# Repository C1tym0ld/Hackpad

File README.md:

# Hackpad

## Pictures

# BOM
- 3d printed Case
- XIAO rp2040
- 10 SK6812 MINI-E LEDs
- 8 Switches
- 8 Key Caps
- 8x Through-hole 1N4148 Diodes 
- M3x16mm screws x4
- M3x5mx4mm heatset inserts x4
- VIA support!

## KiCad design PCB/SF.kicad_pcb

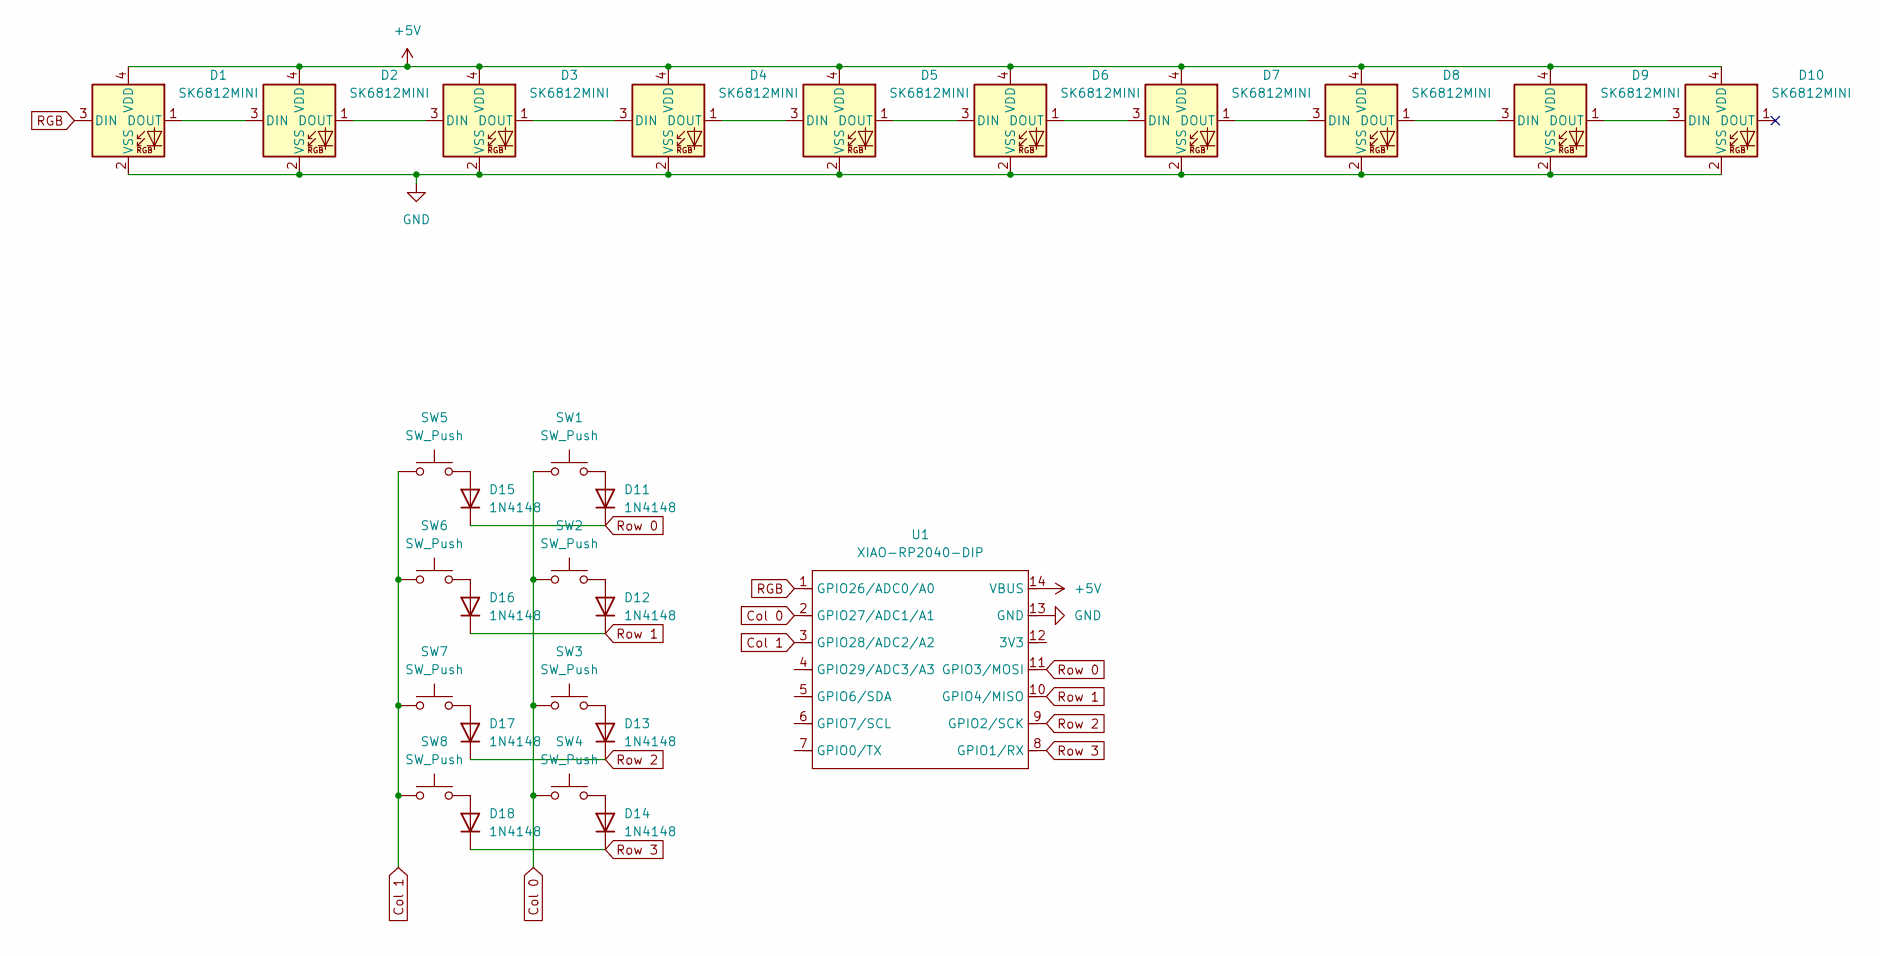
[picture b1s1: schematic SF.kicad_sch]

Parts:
D1, D2, D3, D4, D5, D6, D7, D8, D9, D10: SK6812MINI; LED_SK6812MINI_PLCC4_3.5x3.5mm_P1.75mm
D11, D12, D13, D14, D15, D16, D17, D18: 1N4148; D_DO-35_SOD27_P7.62mm_Horizontal
SW1, SW2, SW3, SW4, SW5, SW6, SW7, SW8: SW_Push; SW_Cherry_MX_1.00u_PCB
U1: XIAO-RP2040-DIP

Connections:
+5V: D1.4 (VDD), D2.4 (VDD), D3.4 (VDD), D4.4 (VDD), D5.4 (VDD), D6.4 (VDD), D7.4 (VDD), D8.4 (VDD), D9.4 (VDD), D10.4 (VDD), U1.14 (VBUS)
Col 0: SW1.1, SW2.1, SW3.1, SW4.1, U1.2 (GPIO27/ADC1/A1)
Col 1: SW5.1, SW6.1, SW7.1, SW8.1, U1.3 (GPIO28/ADC2/A2)
GND: D1.2 (VSS), D2.2 (VSS), D3.2 (VSS), D4.2 (VSS), D5.2 (VSS), D6.2 (VSS), D7.2 (VSS), D8.2 (VSS), D9.2 (VSS), D10.2 (VSS), U1.13 (GND)
unnamed: D1.1 (DOUT), D2.3 (DIN)
unnamed: D2.1 (DOUT), D3.3 (DIN)
unnamed: D3.1 (DOUT), D4.3 (DIN)
unnamed: D4.1 (DOUT), D5.3 (DIN)
unnamed: D5.1 (DOUT), D6.3 (DIN)
unnamed: D6.1 (DOUT), D7.3 (DIN)
unnamed: D7.1 (DOUT), D8.3 (DIN)
unnamed: D8.1 (DOUT), D9.3 (DIN)
unnamed: D9.1 (DOUT), D10.3 (DIN)
unnamed: D11.2 (A), SW1.2
unnamed: D12.2 (A), SW2.2
unnamed: D13.2 (A), SW3.2
unnamed: D14.2 (A), SW4.2
unnamed: D15.2 (A), SW5.2
unnamed: D16.2 (A), SW6.2
unnamed: D17.2 (A), SW7.2
unnamed: D18.2 (A), SW8.2
RGB: D1.3 (DIN), U1.1 (GPIO26/ADC0/A0)
Row 0: D11.1 (K), D15.1 (K), U1.11 (GPIO3/MOSI)
Row 1: D12.1 (K), D16.1 (K), U1.10 (GPIO4/MISO)
Row 2: D13.1 (K), D17.1 (K), U1.9 (GPIO2/SCK)
Row 3: D14.1 (K), D18.1 (K), U1.8 (GPIO1/RX)

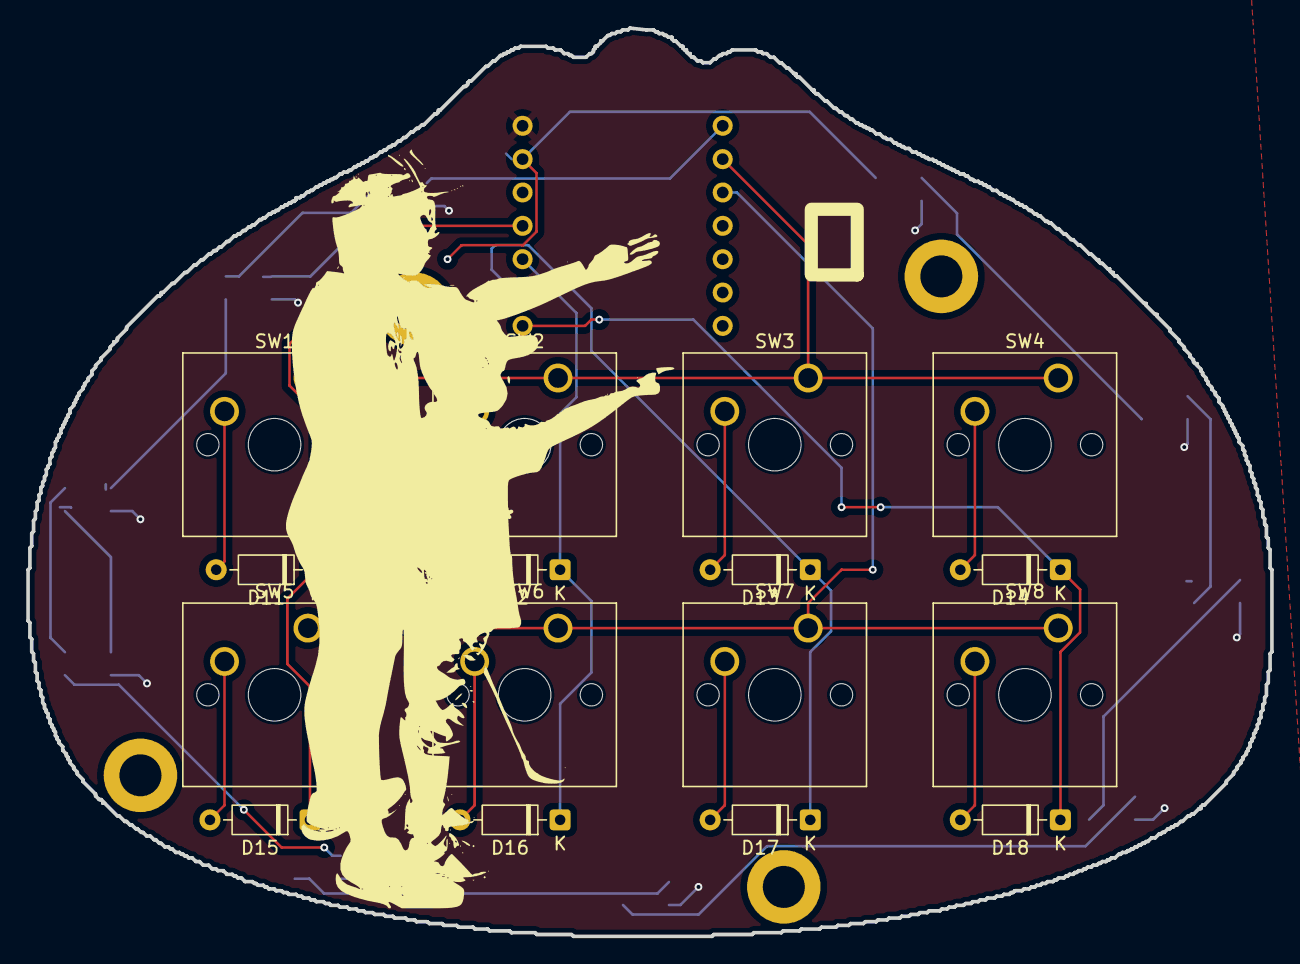
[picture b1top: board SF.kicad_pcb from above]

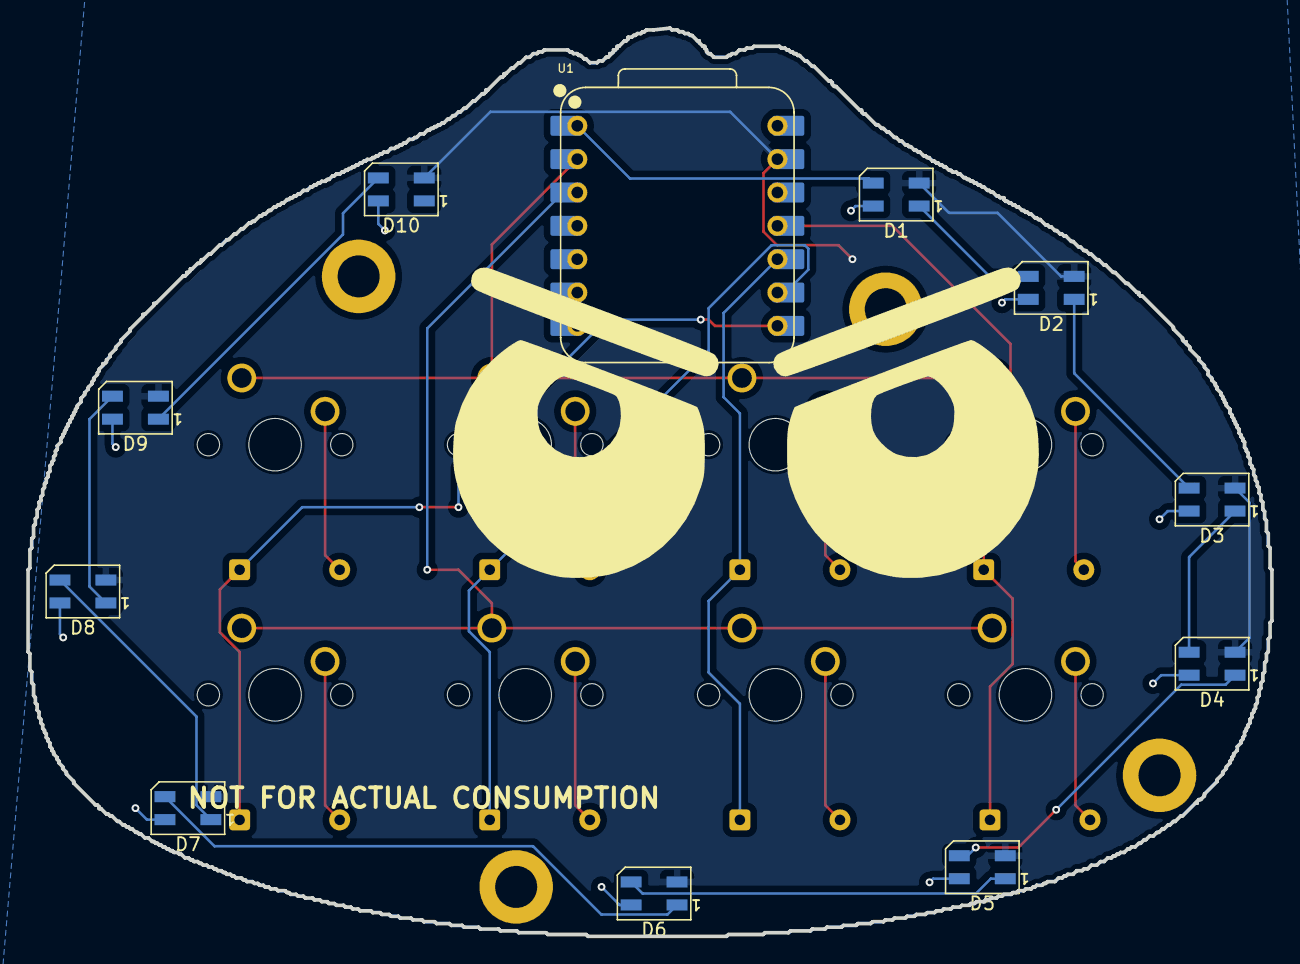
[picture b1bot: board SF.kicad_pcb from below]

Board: 2 copper layers, 94.7 x 69.2 mm, 28 parts (12 on the bottom side), 26 nets.

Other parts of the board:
.: LOGO; eyes1

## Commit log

2025-06-29 Rename Screenshot 2025-06-28 214448.png to screenshot/hackpad.png
2025-06-29 Rename Screenshot 2025-06-28 214817.png to screenshot/schematic.png
2025-06-29 Rename Screenshot 2025-06-28 215138.png to PCB.png
2025-06-29 Rename Screenshot 2025-06-28 215605.png to screenshot/case.png
2025-06-29 Rename Screenshot 2025-06-29 151551.png to schematic.png
2025-06-29 Rename Screenshot 2025-06-29 151806.png to PCB.png
